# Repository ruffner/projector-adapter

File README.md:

# projector-adapter

ProjectorAdapter is a solution for timing camera exposure time with a Digital Micromirror Device (DMD) trigger signal for use in 3D recording.

The completed solution, show below, is connected to the projector with the bottom two cables, with the camera trigger cable out the top.

### Hardware
The firmware runs on a [Teensy 3.2](https://www.pjrc.com/store/teensy32.html).

A custom made PCB was made with the same footprint as the Teensy3.2 with molex connectors for interfacing with a camera and projector DMD.

The PCB sits below the Teensy, with the 6 pin connectors to and from the projector and the 4 pin header routed to the camera trigger cable.

It is written to interface with Ximea cameras using [this](https://www.ximea.com/support/wiki/apis/XiAPI_Camera_Trigger_and_Synchronization_Signals) protocall.

Here is a scope trace of the signals involved: 

### Firmware and operation

The pink trace is the trigger output from the Teensy3.2, at 1Hz with a 10% duty cycle. This signal is routed to the projector. Once the projector has been triggered it sends out trigger pulses (blue), intended to trigger the camera. However, it sends pulses until the next rising edge of its 20% duty cycle trigger signal. This would result in the camera exposing more times than desired.

The solution is to intercept the projector output pulses and only pass one through to the camera. The trigger pulse recreated by the Teensy, seen in yellow, must be centered around the pulse it is replicating to avoid skewing of camera exposure timing.

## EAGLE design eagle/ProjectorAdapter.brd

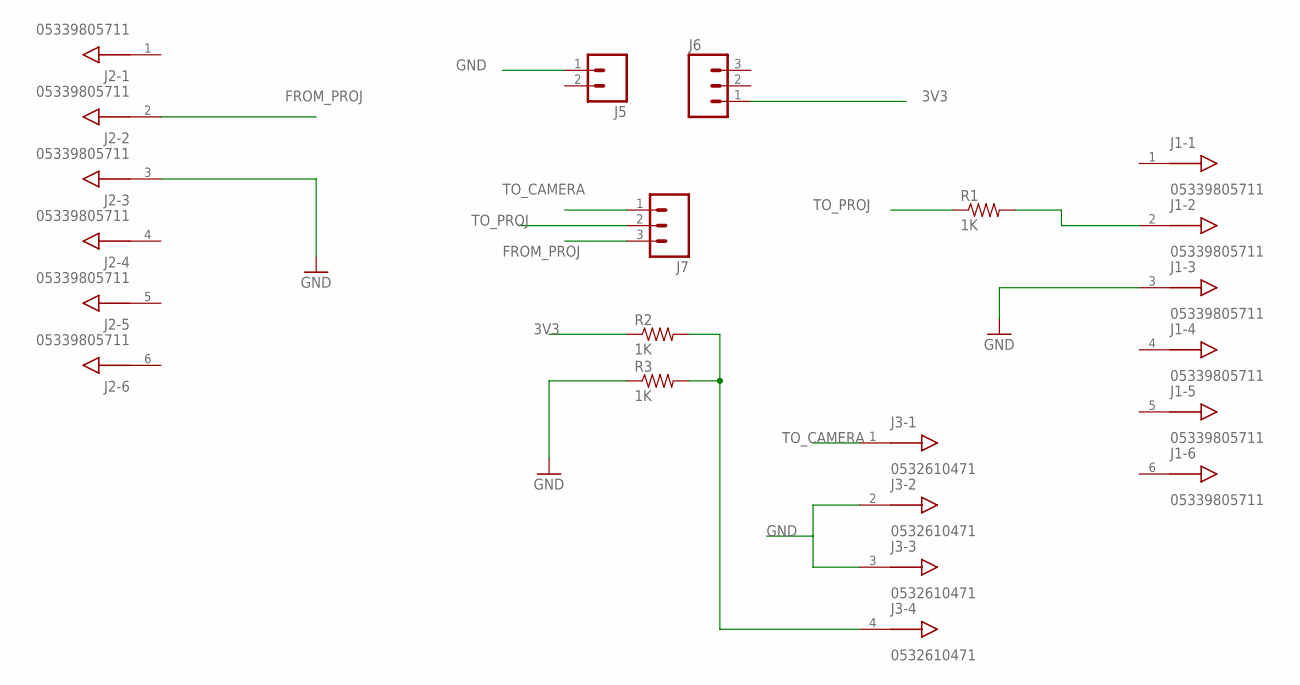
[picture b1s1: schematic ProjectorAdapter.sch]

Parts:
J1, J2: 05339805711; PICOBLADE53398-0671
J3: 0532610471; PICOBLADE53261-0471
J5: M02PTH; 1X02
J6, J7: M03PTH; 1X03
R1, R2, R3: 1K; 0603-RES

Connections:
3V3: J6.1, R2.1
FROM_PROJ: J2.2, J7.3
GND: J1.3, J2.3, J3.2, J3.3, J5.1, R3.1
unnamed: J3.4, R2.2, R3.2
unnamed: J1.2, R1.2
TO_CAMERA: J3.1, J7.1
TO_PROJ: J7.2, R1.1

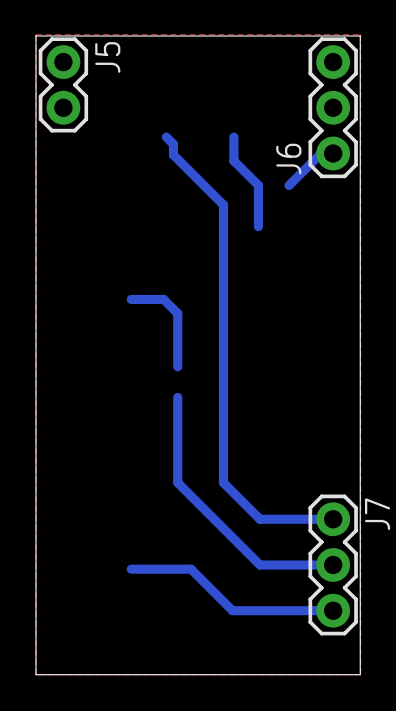
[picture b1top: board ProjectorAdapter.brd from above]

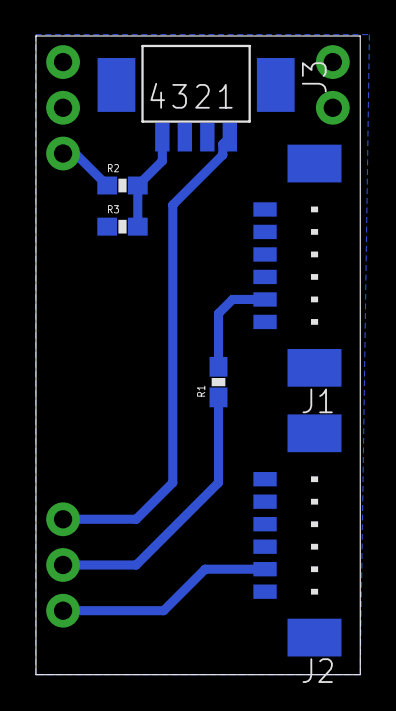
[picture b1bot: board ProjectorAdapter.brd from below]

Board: 2 copper layers, 18.0 x 35.5 mm, 9 parts (6 on the bottom side), 7 nets.

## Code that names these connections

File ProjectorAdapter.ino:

// Trigger interface between camera
// and projector
// Matt Ruffner 2016

#include <EEPROM.h>

// pin definitions
#define TO_PROJ   15
#define FROM_PROJ 14
#define TO_CAMERA 16
#define LED       13

#define ID_LEN 11
#define ID_STRING "MR2016v001"

#define TIMEOUT 5000

#define COMMAND_STATUS    '?'
#define COMMAND_CONFIG    'c'
#define COMMAND_RELOAD    'r'
#define COMMAND_SAVE      's'

// not including newline
#define PACKET_SIZE 12

// setting value addresses in EEPROM
#define ADDR_EXP_RATE   12
#define ADDR_EXP_TIME   16
#define ADDR_DUTY_CYCLE 20

unsigned long t_off = 900;  // in ms
unsigned long t_on  = 100;
unsigned long t_exp  = 16;


struct BUFFER {
  unsigned long expRate, expTime, dutyCycle;
};

BUFFER settings;

void setup() {
  Serial.begin(9600);

  // configure i/o
  setupPins();

  // update settings from EEPROM
  readConfigVals();

  generateTimingValues();

  Serial.println("Finished Setup");
  blinkOK();
}

void loop() {
  
  if ( Serial.available() ) handleSerial();

  unsigned long now = millis();

  digitalWrite( TO_PROJ, HIGH );

  while ( !Serial.available() && millis() - now < t_on);
  if (Serial.available()) handleSerial();

  digitalWrite( TO_PROJ, LOW );
  // projector sends back trigger pulses
  // after falling edge

  // timestamp to avoid time out if projector
  // never responds


  // wait until the projector sends the first
  // of the trigger pulses
  //while( !digitalRead( FROM_PROJ ) && millis()-now < t_off );

  now = millis();
  while ( !Serial.available() && millis() - now < t_on && !digitalRead( FROM_PROJ ));
  if (Serial.available()) handleSerial();

  // trigger pulse is wide enough we don't
  // have to worry about it falling before we check here
  if ( digitalRead( FROM_PROJ ) ) {

    // wait till we go low
    while ( digitalRead( FROM_PROJ ) );
    delayMicroseconds(t_exp - 1);

    // pass the pulse on to the camera
    // status blink too
    digitalWrite( TO_CAMERA, HIGH );
    digitalWrite(LED, HIGH);
    delay(t_exp);
    digitalWrite( TO_CAMERA, LOW );
    digitalWrite(LED, LOW);

    // idle and ignore the rest of the pulses
    // from the projector
    //while( millis()-now < t_off );
  }
  while ( millis() - now < t_off );
}

void handleSerial() {
  char c = COMMAND_STATUS;

  c = Serial.read();

  switch ( c ) {
    case COMMAND_STATUS:
      // to populate software fields
      sendConfig();
      blinkOK();
      break;

    case COMMAND_CONFIG:
      if( !parseConfig() )
        blinkError();
      else
        blinkOK();
      break;

    case COMMAND_RELOAD:
      // config stored in EEPROM
      // reset to prior config feature
      readConfigVals();
      blinkOK();
      break;

    case COMMAND_SAVE:
      // save current parameters to EEPROM
      saveConfigVals();
      blinkOK();
      break;
    default:
      blinkError();
  }

  generateTimingValues();

  // flush newline
  if( Serial.peek() == '\n' )
    Serial.read();
}

void generateTimingValues() {
  double t_on_frac = ((double)settings.dutyCycle)/((double)100.0);
  double t_off_frac = 1.0 - t_on_frac;
  
  t_on = (unsigned long)((double)settings.expRate*t_on_frac);
  t_off = (unsigned long)((double)settings.expRate*t_off_frac);
  t_exp = settings.expTime;
}

bool parseConfig() {
  settings.expRate = (unsigned long)Serial.parseInt();
  settings.expTime = (unsigned long)Serial.parseInt();
  settings.dutyCycle = (unsigned long)Serial.parseInt();

  if( settings.expRate != 0 && settings.expTime != 0 && settings.dutyCycle != 0 ){
    saveConfigVals();
    return true;      
  } else {
    return false;
  }
}

bool sendConfig() {
  String buf = String(ID_STRING) + " " + settings.expRate + String(" ") + settings.expTime + String(" ") + settings.dutyCycle;

  Serial.println(buf);

  return true;
}

void readConfigVals() {
  settings.expRate = readLongFromEEPROM(ADDR_EXP_RATE);
  settings.expTime = readLongFromEEPROM(ADDR_EXP_TIME);
  settings.dutyCycle = readLongFromEEPROM(ADDR_DUTY_CYCLE);
}

void saveConfigVals() {
  writeLongToEEPROM( ADDR_EXP_RATE, settings.expRate );
  writeLongToEEPROM( ADDR_EXP_TIME, settings.expTime );
  writeLongToEEPROM( ADDR_DUTY_CYCLE, settings.dutyCycle );
}

unsigned long readLongFromSerial() {
  return (Serial.read() << 24 |
          Serial.read() << 16 |
          Serial.read() << 8 |
          Serial.read());
}

unsigned long readLongFromEEPROM(uint8_t a) {
  return ( EEPROM.read(a) << 24 |
           EEPROM.read(a + 1) << 16 |
           EEPROM.read(a + 2) << 8 |
           EEPROM.read(a + 3) );
}

void writeLongToEEPROM(uint8_t a, unsigned long d) {
  EEPROM.write(a, (uint8_t)(d >> 24));
  EEPROM.write(a + 1, (uint8_t)(d >> 16));
  EEPROM.write(a + 2, (uint8_t)(d >> 8));
  EEPROM.write(a + 3, (uint8_t)(d));
}

void setupPins() {
  // trigger signal to projector
  pinMode( TO_PROJ, OUTPUT );

  // camera trigger signal from projector
  // we debounce this and pass pulse to camera
  pinMode( FROM_PROJ, INPUT );

  // trigger line to camera
  pinMode( TO_CAMERA, OUTPUT );

  // onboard status LED
  pinMode( LED, OUTPUT) ;
}

void blinkOK() {
  digitalWrite(LED, HIGH);
  delay(1000);
  digitalWrite(LED, LOW);
}

void blinkError() {
  for ( int i = 0; i < 5; i++ ) {
    digitalWrite(LED, HIGH);
    delay(150);
    digitalWrite(LED, LOW);
    delay(50);
  }
}

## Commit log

2016-09-19 added existing work
2016-09-22 updated pcb with molex connectors; created 6 pin connector. updated code for different pin definitions.
2016-09-22 made enclosure more shallow
2016-09-23 designed rev3 board to cover full teensy bottom and mount below it.
2016-09-27 updated code for v3 pcb
2016-09-29 added v3 PCB image and scope trace.
2016-09-29 changing image
2016-09-29 added new PCB image
2016-09-29 image swap
2016-09-29 finally added new pcb image
2016-10-10 added beggining of qt control app
2016-10-11 more work on qt gui
2016-10-11 Serial interface tested through serial terminal
2016-10-11 more gui work
2016-10-21 save/reload functionality working.
2016-10-24 firmware working with gui
2016-11-07 updated to recent scope trace. updated readme accordingly
2016-11-26 added pic of v3 pcb in action
2019-03-01 added old silk changes

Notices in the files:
parts and their libraries:
SparkFun-Connectors: Licensing: Creative Commons ShareAlike 4.0 International - https://creativecommons.org/licenses/by-sa/4.0
volks73-Molex: Creative Commons Attribution-ShareAlike 3.0 Unported (CC BY-SA 3.0), http://creativecommons.org/licenses/by-sa/3.0/.
